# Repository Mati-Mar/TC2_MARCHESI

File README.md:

# Teoría de Circuitos II

Repositorio de trabajos prácticos y tareas semanales de la materia **Teoría de Circuitos II**.

## Estructura

Cada trabajo práctico y tarea semanal se encuentra organizado en su propia carpeta. 
Dentro de cada una se incluyen el desarrollo en Jupyter Notebook y los archivos necesarios para su realización.

* `tarea_semanal_X/`
  Desarrollo de cada tarea semanal, incluyendo análisis teórico, cálculos y conclusiones.

  * `programas/`: scripts y simulaciones utilizados en el desarrollo.
    * `python/`: programas para análisis de sistemas, gráficos, cálculos, etc.
    * `spice/`: simulaciones y modelos utilizados en LTSpice.
  * `recursos/`: material complementario utilizado en la tarea, como imágenes, documentación, consignas y hojas de datos.

* `TPLX/`
  Desarrollo de cada trabajo práctico de laboratorio, incluyendo análisis teórico, cálculos, simulaciones, mediciones, resultados y conclusiones.

  Cada TPL puede contener archivos adicionales específicos del trabajo, como diseños de circuitos o placas PCB.

## Herramientas utilizadas

* Python (SciPy, Matplotlib, pytc2)
* LTSpice
* Jupyter Notebook
* KiCad

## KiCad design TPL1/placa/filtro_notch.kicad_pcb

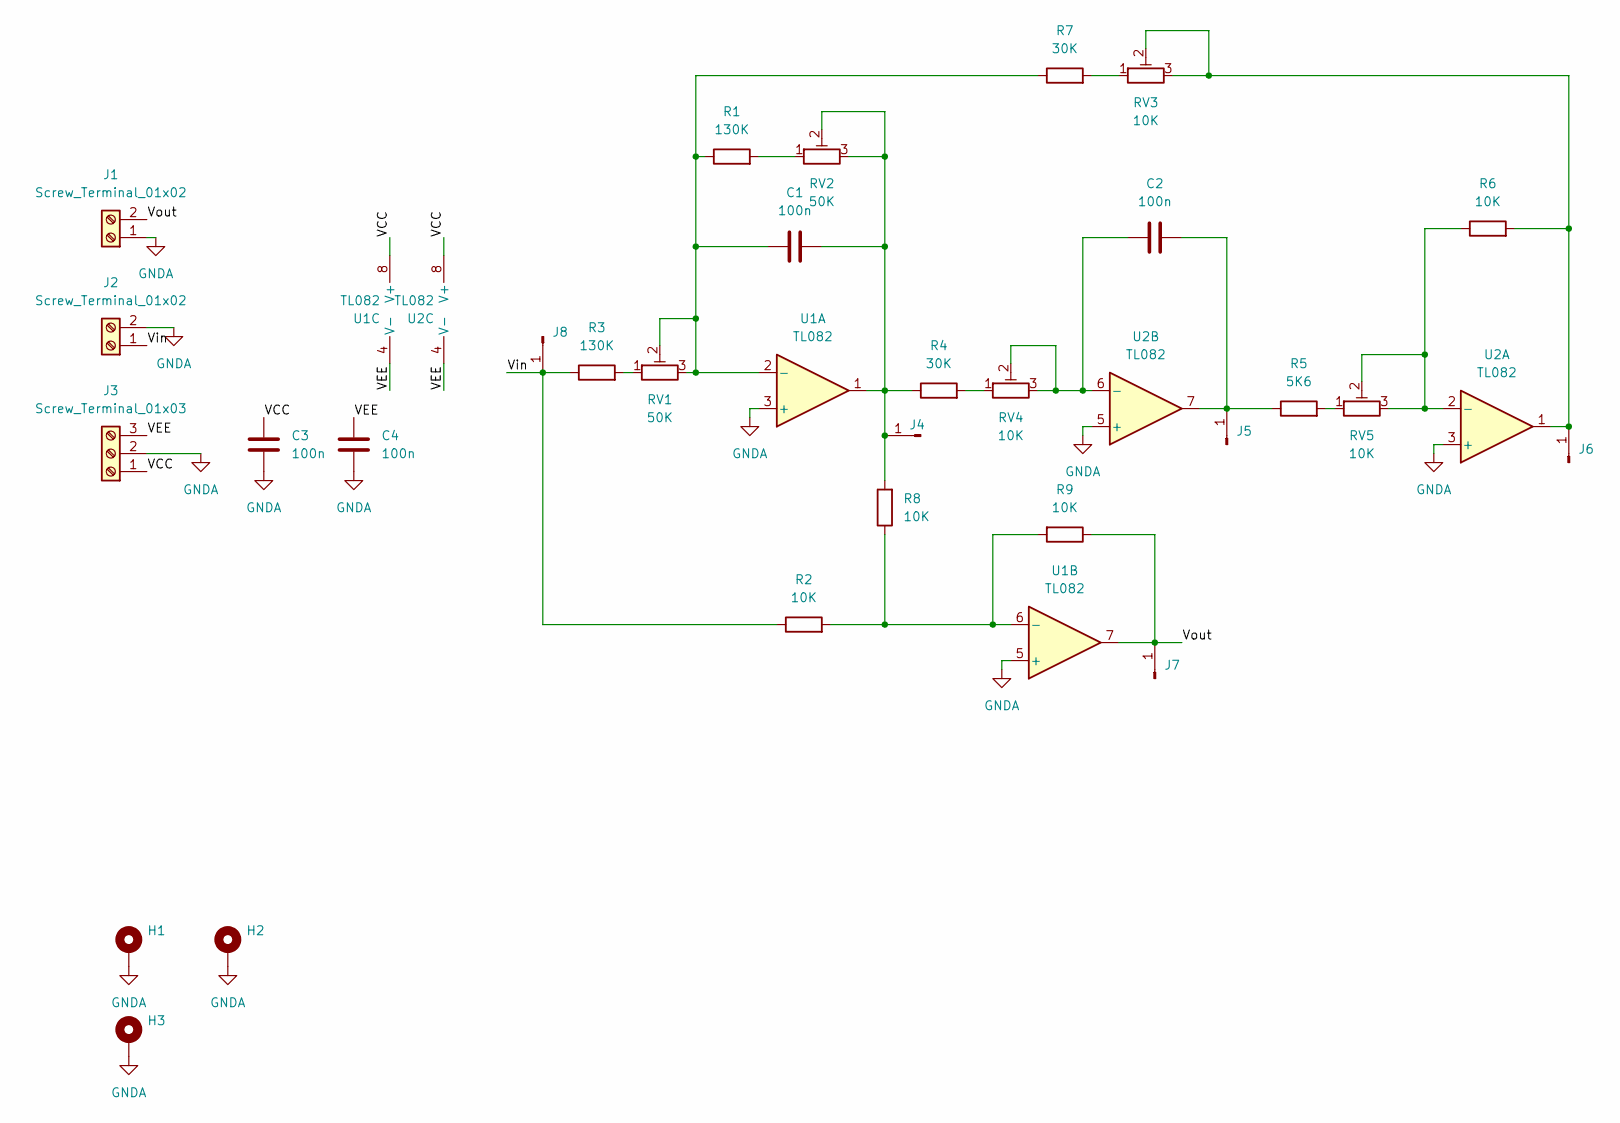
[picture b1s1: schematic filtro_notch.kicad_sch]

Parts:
C1, C2, C3, C4: 100n; C_Disc_D5.0mm_W2.5mm_P5.00mm
H1, H2, H3: MountingHole_Pad; MountingHole_2.5mm_Pad
J1, J2: Screw_Terminal_01x02; TerminalBlock_Phoenix_PT-1,5-2-5.0-H_1x02_P5.00mm_Horizontal
J3: Screw_Terminal_01x03; TerminalBlock_Phoenix_PT-1,5-3-5.0-H_1x03_P5.00mm_Horizontal
J4, J5, J6, J7, J8: Conn_01x01_Pin; PinHeader_1x01_P2.54mm_Vertical
R1, R3: 130K; R_Axial_DIN0207_L6.3mm_D2.5mm_P7.62mm_Horizontal
R2, R6, R8, R9: 10K; R_Axial_DIN0207_L6.3mm_D2.5mm_P7.62mm_Horizontal
R4, R7: 30K; R_Axial_DIN0207_L6.3mm_D2.5mm_P7.62mm_Horizontal
R5: 5K6; R_Axial_DIN0207_L6.3mm_D2.5mm_P7.62mm_Horizontal
RV1, RV2: 50K; Potentiometer_Bourns_3296W_Vertical
RV3, RV4, RV5: 10K; Potentiometer_Bourns_3296W_Vertical
U1, U2: TL082; DIP-8_W7.62mm_LongPads

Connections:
/VCC: C3.2, J3.1, U1.8 (V+), U2.8 (V+)
/VEE: C4.2, J3.3, U1.4 (V-), U2.4 (V-)
/Vin: J2.1, J8.1, R2.1, R3.1
/Vout: J1.2, J7.1, R9.1, U1.7
GNDA: C3.1, C4.1, H1.1, H2.1, H3.1, J1.1, J2.2, J3.2, U1.3 (+), U1.5 (+), U2.3 (+), U2.5 (+)
unnamed: C1.2, J4.1, R4.1, R8.2, RV2.2, RV2.3, U1.1
unnamed: C2.2, J5.1, R5.1, U2.7
unnamed: J6.1, R6.2, RV3.2, RV3.3, U2.1
unnamed: R1.2, RV2.1
unnamed: R3.2, RV1.1
unnamed: R4.2, RV4.1
unnamed: R5.2, RV5.1
unnamed: R7.2, RV3.1
unnamed: C1.1, R1.1, R7.1, RV1.2, RV1.3, U1.2 (-)
unnamed: R2.2, R8.1, R9.2, U1.6 (-)
unnamed: R6.1, RV5.2, RV5.3, U2.2 (-)
unnamed: C2.1, RV4.2, RV4.3, U2.6 (-)

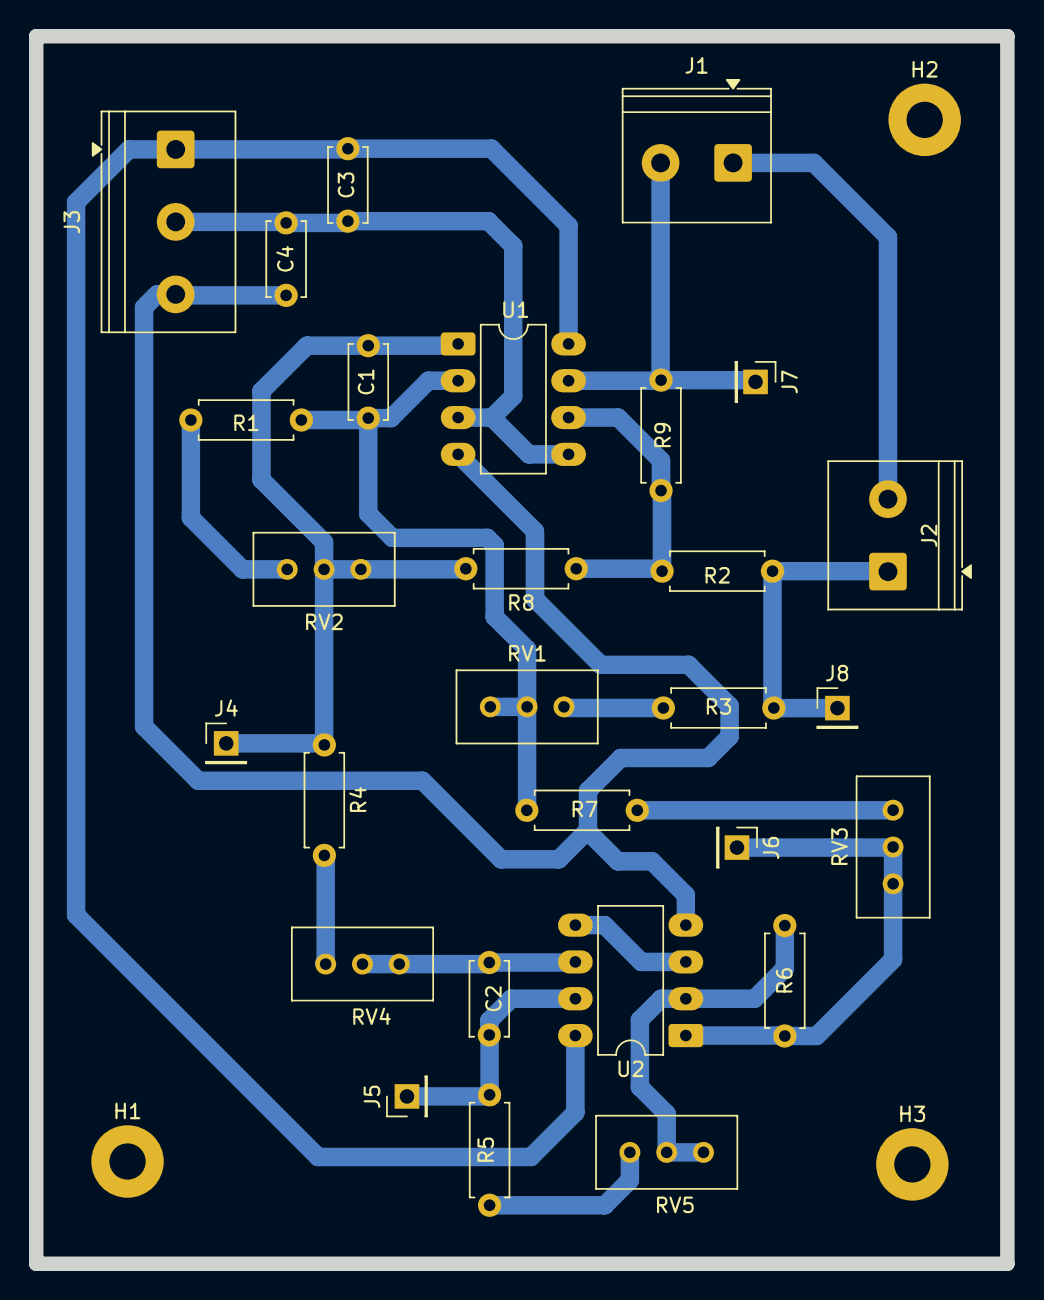
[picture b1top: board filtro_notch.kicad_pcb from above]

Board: 2 copper layers, 67.0 x 84.7 mm, 31 parts (0 on the bottom side), 17 nets.

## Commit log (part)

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2026-04-20 mmarchesi - 20/04/2026
    Se sube tarea semanal 1 con la resolución de un filtro pasatodo
    Se agrega el notebook redactado en jupyter
    Se agregan simulaciones en LTSpice y Python
2026-04-20 Mati-Mar 20/04/26
    Se actualiza el README.md
2026-04-29 Mati-Mar - 29/04/2026
    * Se agrega directorio de recursos para las imágenes
    * Se reformatea el README.md
2026-05-04 Mati-Mar - 04/05/2026
    * Se sube tarea semanal 2 en el directorio de tarea_semanal_2
2026-05-08 MatiMar - 08/05/2026
    * Se corrigen los errores de la tarea semanal 1
2026-05-08 MatiMar - 08/05/2026
    * Se agregan los buffer para el circuito de spice de la tarea 2
2026-05-25 MatiMar - 25/05/2026
    * Se sube tarea semanal 3 en el directorio tarea_semanal_3
2026-06-01 MatiMar - 01/06/2026
    * Se sube tarea semanal 4 en el directorio tarea_semanal_4
    * Falta completar el bonus de la desnormalización
2026-06-17 MatiMar - 17/06/2026
    * Se agregan las imágenes de los cursores faltantes
    * Se corrige el circuito del GIC
    * Se corrigen todos los gráficos relacionados con el GIC
